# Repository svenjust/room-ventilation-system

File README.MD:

# Steuerung einer Lüftungsanlage für Wohnhäuser

Diese Steuerung wurde als Ersatz der Originalsteuerung entwickelt.

Das Original war Pluggit P300. Diese Steuerung funktioniert ebenso für Pluggit P450 und viele
weitere Lüftungsanlagen.

Es werden:
1. zwei Lüfter angesteuert und deren Tachosignale ausgelesen
2. vier Temperatursensoren abgefragt
3. Steuerung Abluftventilator zum Frostschutz
4. Optional: Vorheizregister als Frostschutz 
5. Optional: Sommer-Bypass geschaltet
6. Optional: Bis zu zwei Temperatur- und Feuchtigkeitssensore auslesen
7. Optional: Luftqualitätsensor (VOC) und CO2 Sensor auslesen
Die Drehzahlregelung der Lüftermotoren erfolgt durch PID-Regler. Dies sorgt dafür, das die geforderten
Drehzahlen der Lüfter sicher erreicht werden. Die Leistungssteuerung des Vorheizregisters erfolgt
ebenfalls durch einen PID-Regler.

Differenzdrucksensoren werden bisher nicht berücksichtigt.

Die Steuerung ist per LAN (W5100) erreichbar. Als Protokoll wird mqtt verwendet. Über mqtt liefert
die Steuerung Temperaturen, Drehzahlen der Lüfter, Stellung der Bypassklappe, den Status der AntiFreeze
Funktion und sonstige Werte zurück und es können verschiedene Parameter gesetzt werden.

Zusätzlich bietet die Steuerung Unterstützung für TFT Touchscreen, um einerseits die Messwerte
anzuzeigen und andererseits die Steuerung zu konfigurieren. Touchkalibrierung erfolgt bei dem
ersten Touch oder nach langen Touch auf Hauptseite (8 Sekunden). Im Verzeichnis Screenshots
befinden sich ein paar [Screenshots](Screenshots/README.md).

Im Verzeichnis Docs befindet sich weitere Dokumentation zu verschiedenen Themen.

Um das Projekt zu bauen müssen folgende Voraussetzungen erfüllt sein:
  - Folgende Libraries müssen installiert werden: SPI, EEPROM, PubSubClient,
    Adafruit_GFX_Library, DHT_sensor_library, PID, Adafruit_TouchScreen,
    DallasTemperature, Adafruit_Unified_Sensor, MCUFRIEND_kbv, OneWire,
    Wire, Ethernet
  - Das Projekt bringt eigene Libraries mit. Diese müssen ebenfalls installiert
    werden, am einfachsten als symbolische Links. Der Skript link_libs.sh
    linkt die Libraries an die (hoffentlich) richtige Stelle.

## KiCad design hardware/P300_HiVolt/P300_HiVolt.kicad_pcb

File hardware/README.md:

Änderungen von HW-0.25 zu HW-0.26 - P300_Arduino_IF
 - Korrektur externer Displayanschluss zum Arduino

Änderungen von HW-0.23 zu HW-0.26 - P300_Display_IF
 - Korrektur Displayanschluss zum Display
 
Änderungen von HW-0.23 zu HW-0.25 - P300_Arduino_IF
 - Ergänzung von externen Pullup-Widerstand und Glättungskondensator am Tachosignal

Neu HW-0.25 - P300_Diff_Press
 - Entwurf einer Platine für den Aufbau von Differenzdrucksensoren
 
-----------------------------------------------------------------------------------------------------
12.01.2019 Version HW-0.24, nur P300_HiVolt, in die Platinenerstellung gegeben

Änderungen von HW-0.23 zu HW-0.24 - P300_HiVolt
 - Anschluss zu Relais per Schraubklemmen, anstatt Molex Stecker, wegen der schwierigen Beschaffung und Crimpen der Molex Verbindung
 - Alternative für 5V Spannung Meanwell IRM-05-5 mit 5W(1A) Leistung hinzugefügt, empfohlen bei Verwendung Display
 - Platine 3mm verlängert
 - Bohr in Mitte/unten hinzugefügt
 - Leiterbahnen zu den Lüftern auf 2mm verbreitert

 -----------------------------------------------------------------------------------------------------
09.01.2019 Version HW-0.23 in die Platinenerstellung gegeben

Änderungen von HW-0.22 zu HW-0.23 - P300_Arduino_IF
 - Linke Seite der Platine vergrößert auf ArduinoMega-Größe
 - Stecker für Displayanschluss ergänzt
 - Fünf weitere Bohrungen für Befestigung ergänzt
 - Leiterbahnen im größeren Abstand zu Durchbohrungen und Bauteilen verlegt
 - Connector für J12 I2C nach links verschoben, damit ausreichend Platz für JTS Stecker
 - Auf dem Stecker J4 sind die beiden Lüfteranschlüsse Lüfter 1 und Lüfter 2 getauscht. Damit ist der Stecker kompatibel zu Pluggit. Der Pluggit-Lüfter-Steuerstecker kann direkt aufgesteckt werden, wenn Molex Stiftleiste - KK - 1x8-polig - Stecker, Molex-Best-Nr. 22272081 verwendet wird.
 - Auf dem Stecker J4 (Lüfteranschluss) die vergessenen Masseverbindungen Pin 4 und Pin 8 ergänzt.

Änderungen von HW-0.22 zu HW-0.23 - P300_HiVolt
 - 230V Lüfteranschluss kompatibel zu Pluggit, Molex Stiftleiste - Mini-Fit Jr - 2x4-polig - Stecker, Molex-Best-Nr. 39281083
 - Stecker J3, J4 für Relais auf Molex Stiftleiste - Mini-Fit Jr - 2x3-polig - Stecker, Molex-Best-Nr. 39288060 geändert.
 - Änderung der Belegung der Stecker J3, J4 für die Verwendung es Relaisboards mit den Ralaisanschlüssen: Mitte = Stromzuführung, links = Nicht geschaltet, rechts geschaltet
 - Räumliche Trennung von 230V und Niedervoltspannungen auf der Platine
 - Bohrungen Pins Varistor auf 1mm vergrößert
 
Neu HW-0.23 - P300_Display_IF
 - Platine zum Aufstecken des Displays für die räumlich getrennte Montage von Display zu P300_Arduino_IF
 - Bohrlöcher für Befestigung hinzugefügt

Änderungen von HW-0.20 zu HW-0.21 - P300_Arduino_IF
 - Pins für Relais auf die ursprünglichen Pins zurückgelegt:
   D40 = BP_DIR, D41 = BP_POW, D42 = L2, D43 = L1
 - Pins für PWM-Signal Lüfter auf ursprüngliche Belegung zurückgelegt
   D44 = PWM_L1, D46 = PWM_L2

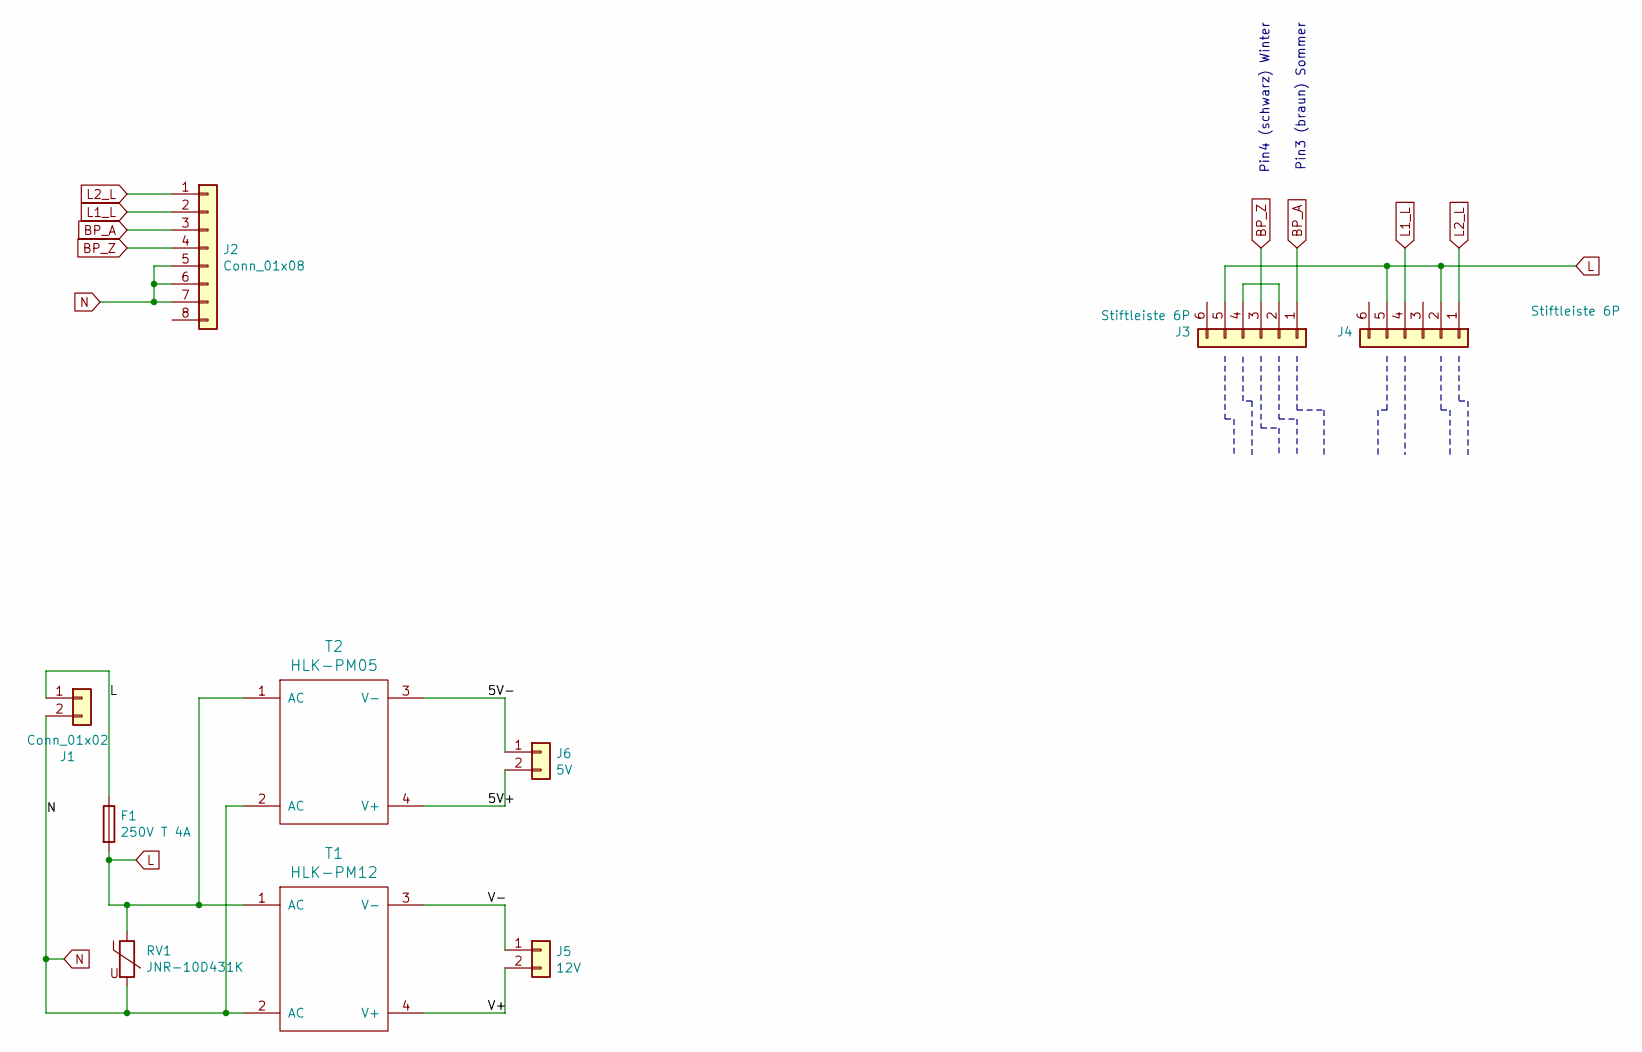
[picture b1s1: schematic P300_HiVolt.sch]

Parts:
F1: 250V T 4A; Fuseholder_TR5_Littlefuse_No560_No460
J1: Conn_01x02; Molex_Mini-Fit_Jr_5566-02A_2x01_P4.20mm_Vertical
J2: Conn_01x08; Molex_Mini-Fit_Jr_5566-08A_2x04_P4.20mm_Vertical
J3, J4: Stiftleiste 6P; TerminalBlock_bornier-6_P5.08mm
J5: 12V; Molex_KK-254_AE-6410-02A_1x02_P2.54mm_Vertical
J6: 5V; Molex_KK-254_AE-6410-02A_1x02_P2.54mm_Vertical
RV1: JNR-10D431K; RV_Disc_D12mm_W7.5mm_P7.5mm
T1: HLK-PM12
T2: HLK-PM05; HLK-PM12

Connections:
/5V+: J6.2, T2.4 (V+)
/5V-: J6.1, T2.3 (V-)
/V+: J5.2, T1.4 (V+)
/V-: J5.1, T1.3 (V-)
BP_A: J2.3, J3.1
BP_Z: J2.4, J3.3
L: F1.1, F1.2, J1.1, J3.5, J4.2, J4.5, RV1.1, T1.1 (AC), T2.1 (AC)
L1_L: J2.2, J4.4
L2_L: J2.1, J4.1
N: J1.2, J2.5, J2.6, J2.7, RV1.2, T1.2 (AC), T2.2 (AC)
unnamed: J3.2, J3.4

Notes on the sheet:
Pin3 (braun) Sommer
Pin4 (schwarz) Winter

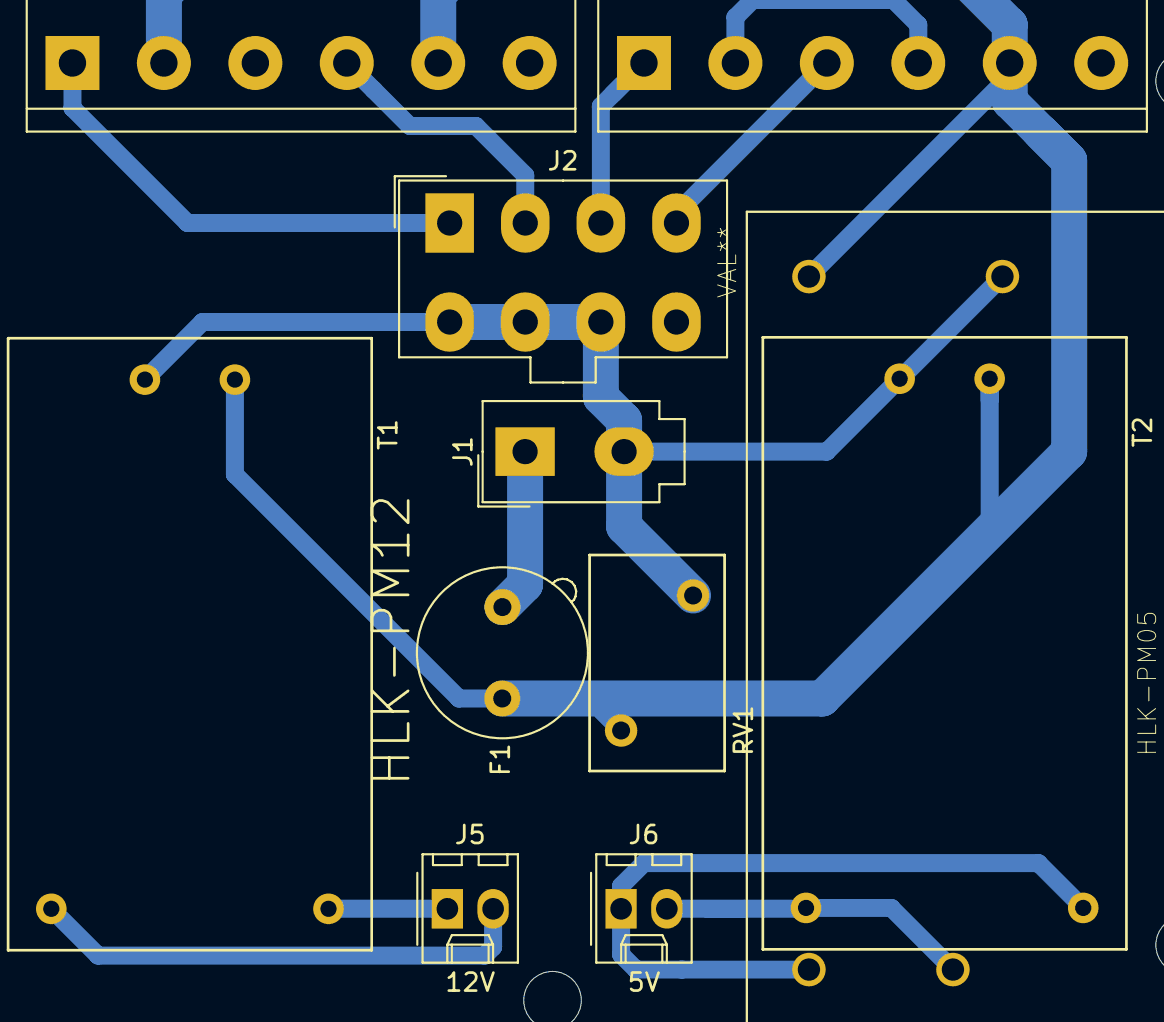
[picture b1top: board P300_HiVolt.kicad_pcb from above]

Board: 2 copper layers, 11 parts (0 on the bottom side), 11 nets.

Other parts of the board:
Meanwell IRM-05-5: VAL**; CONV_IRM-05-5

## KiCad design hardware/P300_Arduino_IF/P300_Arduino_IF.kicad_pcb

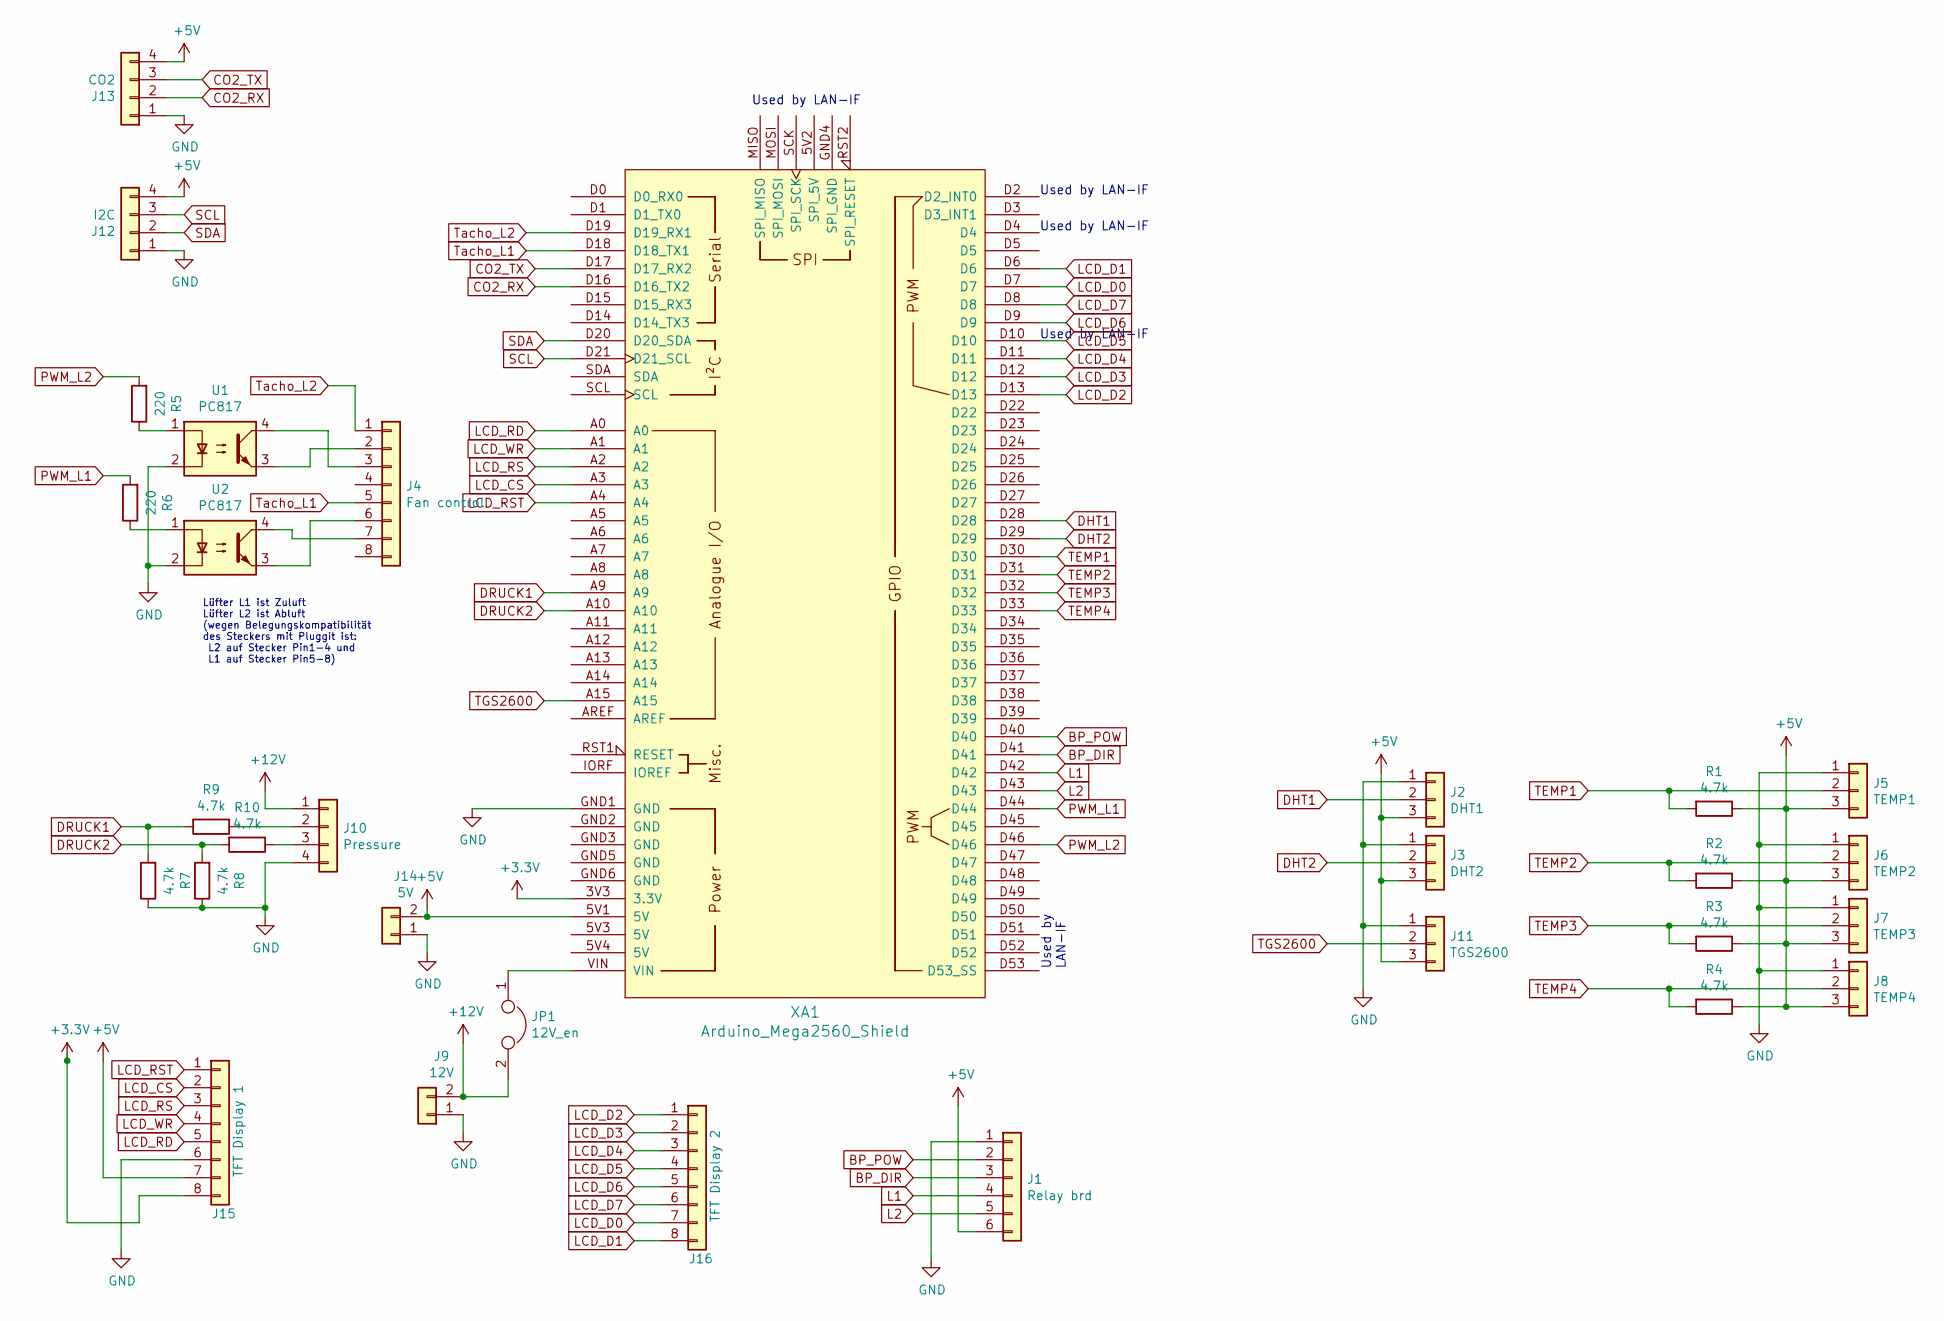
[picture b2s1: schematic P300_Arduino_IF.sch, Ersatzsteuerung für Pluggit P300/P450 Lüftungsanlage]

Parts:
J1: Relay brd; Molex_KK-254_AE-6410-06A_1x06_P2.54mm_Vertical
J2: DHT1; Molex_KK-254_AE-6410-03A_1x03_P2.54mm_Vertical
J3: DHT2; Molex_KK-254_AE-6410-03A_1x03_P2.54mm_Vertical
J4: Fan control; Molex_KK-254_AE-6410-08A_1x08_P2.54mm_Vertical
J5: TEMP1; Molex_KK-254_AE-6410-03A_1x03_P2.54mm_Vertical
J6: TEMP2; Molex_KK-254_AE-6410-03A_1x03_P2.54mm_Vertical
J7: TEMP3; Molex_KK-254_AE-6410-03A_1x03_P2.54mm_Vertical
J8: TEMP4; Molex_KK-254_AE-6410-03A_1x03_P2.54mm_Vertical
J9: 12V; Molex_KK-254_AE-6410-02A_1x02_P2.54mm_Vertical
J10: Pressure; Molex_KK-254_AE-6410-04A_1x04_P2.54mm_Vertical
J11: TGS2600; Molex_KK-254_AE-6410-03A_1x03_P2.54mm_Vertical
J12: I2C; Molex_KK-254_AE-6410-04A_1x04_P2.54mm_Vertical
J13: CO2; Molex_KK-254_AE-6410-04A_1x04_P2.54mm_Vertical
J14: 5V; Molex_KK-254_AE-6410-02A_1x02_P2.54mm_Vertical
J15: TFT Display 1; Molex_KK-6410-08_08x2.54mm_Straight
J16: TFT Display 2; Molex_KK-254_AE-6410-08A_1x08_P2.54mm_Vertical
JP1: 12V_en; PinHeader_1x02_P2.54mm_Vertical
R1, R2, R3, R4: 4.7k; R_Axial_DIN0207_L6.3mm_D2.5mm_P10.16mm_Horizontal
R5, R6: 220; R_Axial_DIN0207_L6.3mm_D2.5mm_P2.54mm_Vertical
R7, R8, R9, R10: 4.7k; R_Axial_DIN0207_L6.3mm_D2.5mm_P2.54mm_Vertical
U1, U2: PC817; DIP-4_W7.62mm
XA1: Arduino_Mega2560_Shield; Arduino_Mega2560_Shield_no_ICSP

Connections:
+3V3: J15.8, XA1.3V3 (3.3V)
+5V: J1.6, J2.3, J3.3, J5.3, J6.3, J7.3, J8.3, J11.3, J12.4, J13.4, J14.2, J15.7, R1.1, R2.1, R3.1, R4.1, XA1.5V1 (5V)
+12V: J9.2, J10.1, JP1.2
BP_DIR: J1.3, XA1.D41
BP_POW: J1.2, XA1.D40
CO2_RX: J13.2, XA1.D16 (D16_TX2)
CO2_TX: J13.3, XA1.D17 (D17_RX2)
DHT1: J2.2, XA1.D28
DHT2: J3.2, XA1.D29
DRUCK1: R7.2, R9.2, XA1.A9
DRUCK2: R8.2, R10.2, XA1.A10
GND: J1.1, J2.1, J3.1, J4.4, J4.8, J5.1, J6.1, J7.1, J8.1, J9.1, J10.4, J11.1, J12.1, J13.1, J14.1, J15.6, R7.1, R8.1, U1.2, U2.2, XA1.GND1 (GND)
L1: J1.4, XA1.D42
L2: J1.5, XA1.D43
LCD_CS: J15.2, XA1.A3
LCD_D0: J16.7, XA1.D7
LCD_D1: J16.8, XA1.D6
LCD_D2: J16.1, XA1.D13
LCD_D3: J16.2, XA1.D12
LCD_D4: J16.3, XA1.D11
LCD_D5: J16.4, XA1.D10
LCD_D6: J16.5, XA1.D9
LCD_D7: J16.6, XA1.D8
LCD_RD: J15.5, XA1.A0
LCD_RS: J15.3, XA1.A2
LCD_RST: J15.1, XA1.A4
LCD_WR: J15.4, XA1.A1
unnamed: J4.2, U1.3
unnamed: J4.3, U1.4
unnamed: J4.6, U2.3
unnamed: J4.7, U2.4
unnamed: J10.2, R9.1
unnamed: J10.3, R10.1
unnamed: JP1.1, XA1.VIN
unnamed: R5.1, U1.1
unnamed: R6.1, U2.1
PWM_L1: R6.2, XA1.D44
PWM_L2: R5.2, XA1.D46
SCL: J12.3, XA1.D21 (D21_SCL)
SDA: J12.2, XA1.D20 (D20_SDA)
TEMP1: J5.2, R1.2, XA1.D30
TEMP2: J6.2, R2.2, XA1.D31
TEMP3: J7.2, R3.2, XA1.D32
TEMP4: J8.2, R4.2, XA1.D33
TGS2600: J11.2, XA1.A15
Tacho_L1: J4.5, XA1.D18 (D18_TX1)
Tacho_L2: J4.1, XA1.D19 (D19_RX1)

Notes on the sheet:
Used by LAN-IF
Used by LAN-IF
Lüfter L1 ist Zuluft Lüfter L2 ist Abluft (wegen Belegungskompatibilität des Steckers mit Pluggit ist: L2 auf Stecker Pin1-4 und L1 auf Stecker Pin5-8)

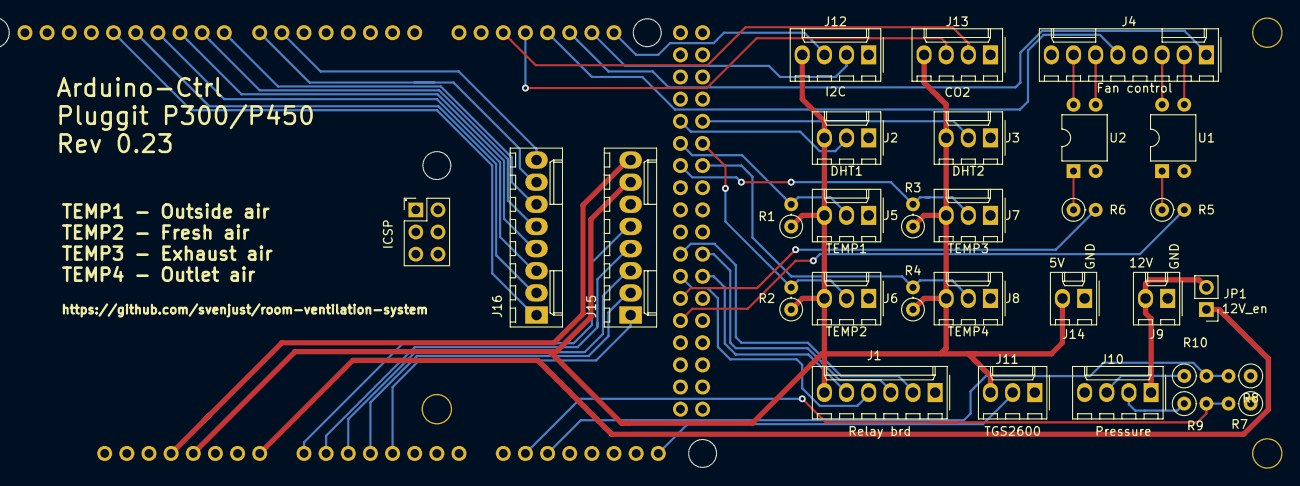
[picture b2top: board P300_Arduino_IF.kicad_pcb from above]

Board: 2 copper layers, 31 parts (0 on the bottom side), 47 nets.

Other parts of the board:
ICSP: Pin_Header_Straight_2x03_Pitch2.54mm

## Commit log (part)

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2017-12-09 Debug
2017-12-11 TFT added
2017-12-11 mqtt-Debug Msg
2017-12-11 Debugausgabe per mqtt
2017-12-11 lueftugsstufe wird per mqtt gepublishet
2017-12-12 mqtt Heartbeat implementiert
2017-12-12 Try: tachoPinFan; Zuweisung von Pin und Interrupt unterschieden. digitalPinToInterrupt liefert den Interrupt eines Pins
2017-12-12 Bugfix: Umrechnung von Pin zu Interrupt fehlte
2017-12-14 Bugfixing: AntiFreeze Schaltung
2017-12-14 Erste Version für Lüfter Kalibrierung
2017-12-14 Reset/Werkszustand per mqtt topic d15/set/kwl/resetAll_IKNOWWHATIMDOING
2017-12-14 Kalibrierung per mqtt startbar
2017-12-14 Bugfixing: Kalibrierung per mqtt startbar
2017-12-15 Bugfixing: Grenzwertbetrachtung Lüfteransteuerung
2017-12-15 PIN10 auf PIN53 verlegt in W5100
2017-12-18 Überarbeitung Sourcecode
2017-12-20 Bugfix und Serial.println für Sommer-Bypass
2017-12-22 30 Sekunden pwm Werte sammeln bei Referenzfahrt
2017-12-22 Docs
2017-12-25 TFT Anzeige auf schönere Fonts umgestellt
2017-12-26 Error Check ergänzt
2018-01-01 DHT11 hinzugefügt
2018-01-02 Update Schaltplan
2018-01-02 Netzwerkeinstellungen und Infotext
2018-01-02 bugfix Ansteuerung Vorheizregister
2018-01-02 bugfix
2018-01-14 LAN Shield, Touch eingebaut, einfaches Menüsystem ergänzt
2018-01-16 update mqtt Topics
2018-01-16 Menusystem debugging
2018-01-17 Sensoren und Ausgabe
2018-01-18 Debugging: Menü ohne Taste korrigiert
2018-01-18 VOC Sensor ergänzt
2018-01-20 Bugfixing
2018-01-22 add GPL Header
2018-01-24 Doku
2018-01-24 Readme as pdf file
2018-03-01 EffiencyKwl bei dem mqtt-Topics hinzugefügt. Der Wirkungsgrad wird zusammen mit den Temperaturen per mqtt übertragen
2018-03-01 Korrektur der Ausgabe von Temperaturen zwischen -0.9 und 0 Grad auf dem Display. Diese wurde ohne Vorzeichen als 0 bis 0.9 ausgegeben.
2018-03-06 AntiFreeze - Forstschutzschaltung umgebaut und Kaminbetrieb ergänzt
2018-03-07 AntiFreeze - Forstschutzschaltung umgebaut und Kaminbetrieb ergänzt, Doku
2018-03-13 Bugfixing: Summer Bypass
2018-03-14 Create LICENSE
2018-06-30 More precise fan speed calculation
2018-06-30 Work on cleaning up the source code by explicitly specifying user configuration in a separate file.
    Example on IP address, standard settings and relay control.
    This method has the advantage of using less space for the configuration
    of complex objects (like IP address), since these are just compile-time
    literals instead of real variables. Thus, more RAM space is available
    for useful stuff.
2018-07-03 PR #3, #4
2018-07-03 Update Docu: power suppy for Arduino is 5V pin not Vin
2018-07-03 Update circuit diagram: power suppy for Arduino is 5V pin not Vin
2018-07-05 Move rest of pin definitions to configuration
2018-07-05 Implement a simple cooperative task scheduler
2018-07-05 Move temperature sensors to its own module
2018-07-05 Initialization trace helper to track component initialization before it happens
2018-07-05 Scheduler - own stats
2018-07-05 Handler for persistent configuration in EEPROM
    Also add explicit config for KWL and remove old EEPROM handling
2018-07-05 Add skeleton for MQTT handler
2018-07-05 Move fan control to a new component
2018-07-05 Move MQTT topics definition to a separate header
2018-07-05 Add StringView to ease comparing of strings w/o allocation
2018-07-05 Add statistics for tasks
    Queryable using MQTT message to d15/debugset/kwl/scheduler/getvalues,
    statistics are sent per task to d15/debugstate/kwl/scheduler.
2018-07-09 Zyklische Übertragung von CO2 und VOC per MQTT ergänzt
2018-07-09 Add support for C++14 integer and index sequences
2018-07-09 Create type for storing string literals in Flash as constexpr and support loading them into RAM easily
2018-07-09 Create NetworkClient module
    This required two larger changes:
    - refactoring startup routines a bit, since initialization order w.r.t. libraries was not given
    - storing MQTT topics in Flash, since too little memory was left (obviously before it was just a few bytes short of crashing)
2018-07-09 Move classes to their own headers
2018-07-09 PersistentConfig: add support for migration without incrementing version
2018-07-09 Add microscopic NTP client to get current time + weekday from NTP server
2018-07-09 Simplify scheduler, add poll() method for polling stuff (like network or input)
    Also adjust components accordingly to use it.
2018-07-09 Create small class to hold time in HH:MM:SS format and to print it out
2018-07-09 Add support for resetting runtime maxima in statistics
2018-07-09 Move Antifreeze to its own component
2018-07-09 Rename kwl_config to KWLConfig to match naming conventions elsewhere
2018-07-09 Support comparison of StringView with flash strings
2018-07-09 Allow configuration of fan speed impulse sampling mode
2018-07-09 Rename start() to begin() to match naming convention in other Arduino components
2018-07-09 Support publishing Flash strings on MQTT topics
2018-07-09 Debugausgaben reduziert
2018-07-09 WIP: program manager
2018-07-09 Small fixes and memory reduction
2018-07-11 Add const getters for temperature sensors
2018-07-11 Tasking: add the possibility to set the interval by the task itself
2018-07-11 Message publishing cleanups
2018-07-11 Summer bypass refactoring
    Separate bypass component
    Fix the naming and configuration of temperature hysteresis for antifreeze (it was using bypass as name) + adjust persistent config appropriately
    Add missing MQTT topics to set bypass temperature limits
2018-07-11 Pass StringView as MQTT payload to receive methods
2018-07-12 Add asynchronous MQTT publish task
2018-07-12 Publish MQTT messages asynchronously and safely
2018-07-12 Add possibility to send heartbeat as timestamp
2018-07-13 Send error and info bits via statusbits message, rework error loop
2018-07-14 Remove FL() function, as it is not working properly in all cases. Replace usages appropriately.
2018-07-14 Print EEPROM contents only on serial console, not to TFT
    Also position cursor correctly on TFT during booting
2018-07-14 Add the possibility to write command on serial console to simulate MQTT input (for debugging)
2018-07-14 Significantly reduce number of files in sketch directory
    Move some stuff into libraries inside of the project. Makes building a tick more complex, since the libraries must be linked from Arduino libraries directory (script provided).
2018-07-15 Wrap additional sensor into own class, make it real cpp file
    Still TODO to clean it up - unnecessary millis queries, unsafe MQTT publish, etc.
2018-07-15 Fix network initialization
    Additional debugging for IP addresses and on MQTT receive side
2018-07-19 Add watchdog timer
2018-07-20 Move FlashStringLiteral and StringView to libraries
2018-07-20 Clean up additional sensors - use timed tasks
2018-07-20 Move scheduler to a library
    Also clean up the APIs to make it more generic, so it can be submitted to Arduino libs (not yet so far, but code as such is close to it)
2018-07-21 Clean up MessageHandler - to be moved to libraries
2018-07-21 Join config headers and sources for normal and persistent config together to reduce number of files
2018-07-21 Rework program manager MQTT topics, add documentation
    Also small fixes in string handling and network client
2018-07-22 Support program sets in program manager
2018-07-22 Add crash handler and the possibility to query crashes
2018-07-22 Add support for setting NTP time for debug purposes
2018-07-24 Add scheduler stats to unique topics
    Also improve string handling, which saves memory.
2018-07-24 Fix configuration of strings, simplify user configuration in general
2018-07-24 Report crash via status bits; document crash debugging and status info
2018-07-24 Fix language in summer bypass init
2018-07-24 Fix factory reset - properly overwrite memory
2018-07-24 Fix program selection handling to match documentation
2018-08-15 Fix fan RPM reading when fan stopped
2018-08-17 TFT refactoring
2018-08-17 NTP: add error bit if no NTP server available and upgrade to NTPv4
2018-08-31 Additional sensors: minor corrections for VOC state and serial debug
2018-09-01 Store network config in EEPROM
2018-09-10 TFT: Setup for program data and antifreeze, support screen off
2018-09-10 TFT: Add setup for timezone and DST
2018-09-10 TFT: Rework fan config screen
2018-09-10 TFT: support bypass and IP configuration
2018-09-11 Screenshot support
2018-09-23 Screen calibration
2018-09-23 Do not send erroneous measurements, except if explicitly configured
2018-09-23 Main screen with graphical representation of sensor values
2018-09-23 Add a few screenshots
2018-09-23 TFT: Remove explicit control class, make control a mixin
2018-09-25 TFT: Setup menu with icons, also icons for buttons
    Add screenshots from setup menu and add icons credits.
2018-10-11 TFT: Display program set and current program on main screen
2018-10-11 TFT: Support program set selection
2018-12-06 Update README.MD
    Fehler beim Linken, wenn Arduino AVR Boards Versionen größer 1.6.21 verwendet werden.
2018-12-06 Clean up constexpr usage to compile with Arduino AVR board 1.6.23
2018-12-06 Set VersionString to 0.20 in respect to all changes
2018-12-08 Backup
2018-12-10 CO2 Sensor wurde nach Einschalten nicht erkannt, nur nach Reset. Das Schreiben und Lesen der seriellen Schnittstelle zum CO2 Sensor vorab, behebt den Fehler.
2018-12-23 Ergänzt Schaltplan und Platine, V0.22-dev
2018-12-24 Bilder Aufbau Ctrl Platine V0.22-dev
    Verschiedene Ansichten der Ctrl Platine mit den Steckverbindungen zum Arduino Mega und zum LAN Shield
2019-01-05 Update der Platinen auf 0.23-dev
    Änderungen von 0.22 zu 0.23 - P300_Arduino_IF
    - Linke Seite der Platine vergrößert auf ArduinoMega-Größe
    - Stecker für Displayanschluß ergänzt
    - Fünf weitere Bohrungen für Befestigung ergänzt
    - Leiterbahnen im größeren Abstand zu Durchbohrungen und Bauteilen verlegt
    - Connector für J12 I2C nach links verschoben, damit ausreichend Platz für JTS Stecker
2019-01-07 Masseverbindungen auf J4 ergänzt.
    Auf dem Stecker J4 (Lüfteranschluss) die vergessenen Masseverbindungen Pin 4 und Pin 8 ergänzt.
2019-01-09 Platinen V.23 in die Herstellung gegeben
2019-01-09 Footprint Arduino reduziert
    Für die Displayplatine wird nur eine Teil des Arduino Mega Footprint benötigt.
2019-01-10 Bugfix: TempSensor3 missing t3_.begin();
    Der TempSensor3 wurde nicht gestartet.
2019-01-10 Die maximale Abweichung der Ist- zur Solldrehzahl bei der Kalibrierung der Lüfter kann jetzt in der KWLConfig.h festgelegt werden. Bisher waren fest +/- 10 Umdrehungen erlaubt, damit der tech_setpoin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
2019-01-12 TFT: Display small status on the screensaver screen
    It shows just fan speed at random location on the screensaver screen.
    In case of error, the icon changes to red stop icon, when info is
    available, to yellow triangle icon.
2019-01-13 Change fan multiplier to interrupts per rotation
2019-01-13 SW-Versionsstring hochgezählt auf 0.21
2019-01-14 Update P300_HiVolt Platine
    - Anschluss zu Relais per Schraubklemmen, anstatt Molex Stecker, wegen der schwierigen Beschaffung und Crimpen der Molex Verbindung
    - Alternative für 5V Spannung Meanwell IRM-05-5 mit 5W(1A) Leistung hinzugefügt, empfohlen bei Verwendung Display
    - Platine 3mm verlängert
    - Bohr in Mitte/unten hinzugefügt
    - Leiterbahnen zu den Lüftern auf 2mm verbreitert
2019-01-22 Add Script plotfans.py
    Dieses Python Script liest eine Logdatei mit den Drehzahlen der Lüfter ein und stellt die Werte graphisch dar.
2019-01-24 PID Regelung Lüfter verlangsamt
2019-01-24 PWM Frequenz 490Hz
2019-01-24 Versionsstring hochgezählt auf V0.22
2019-02-17 Update ReadMe
    Aktueller Stand der Platinen berücksichtigt und die Erfahrungen bei der Inbetriebnahme der Anlage mit anderen Ventilatoren
2019-02-17 Platinen Update
    Änderungen von HW-0.25 zu HW-0.26 - P300_Arduino_IF
    - Korrektur externer Displayanschluss zum Arduino
    Änderungen von HW-0.23 zu HW-0.26 - P300_Display_IF
    - Korrektur Displayanschluss zum Display
    Änderungen von HW-0.23 zu HW-0.25 - P300_Arduino_IF
    - Ergänzung von externen Pullup-Widerstand und Glättungskondensator am Tachosignal
